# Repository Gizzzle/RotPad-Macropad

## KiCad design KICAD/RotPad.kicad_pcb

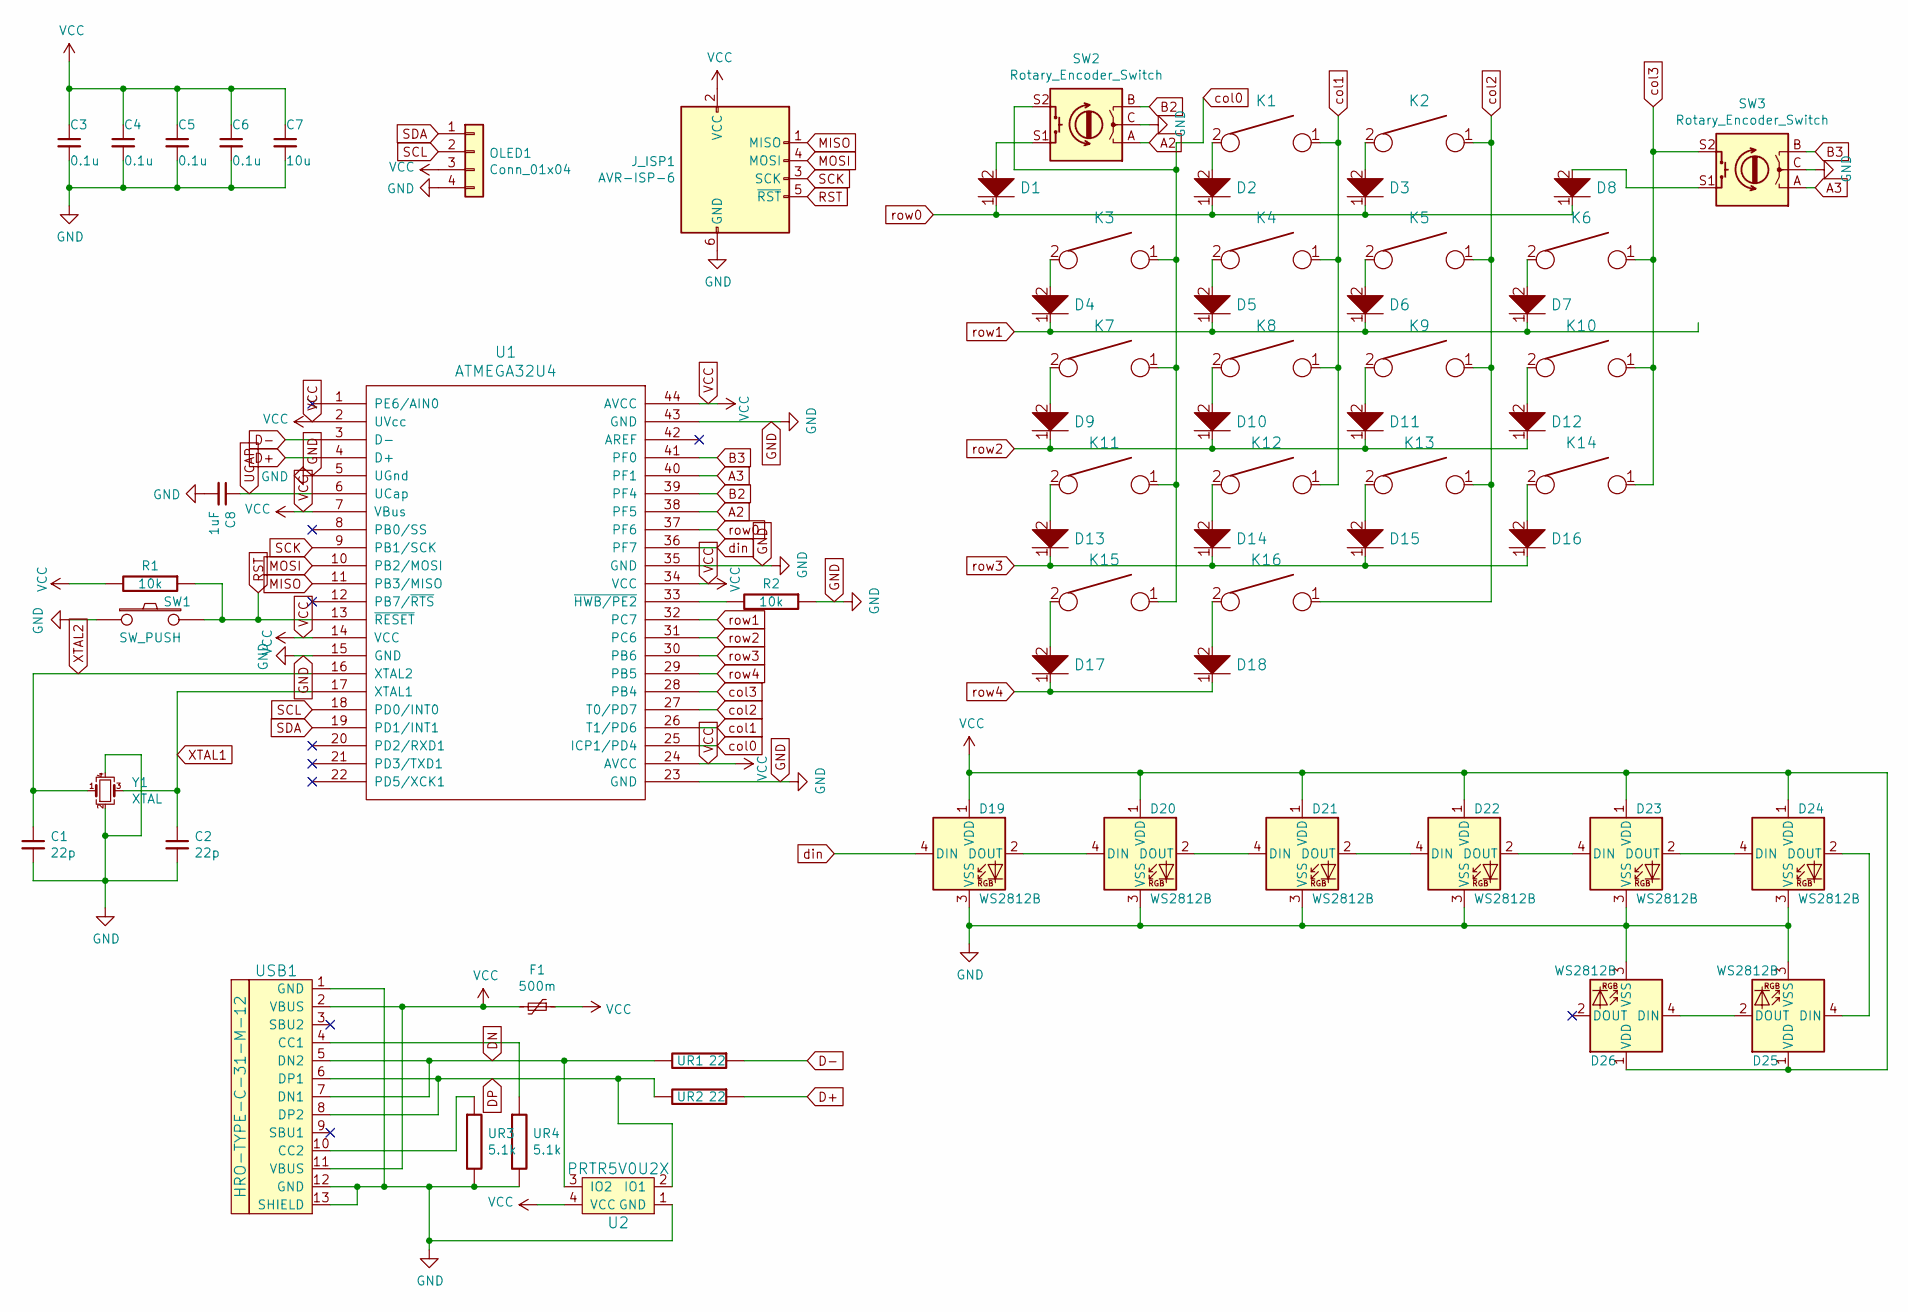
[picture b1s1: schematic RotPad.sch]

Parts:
C1, C2: 22p; C_0805_2012Metric_Pad1.15x1.40mm_HandSolder
C3, C4, C5, C6: 0.1u; C_0805_2012Metric_Pad1.15x1.40mm_HandSolder
C7: 10u; C_0805_2012Metric_Pad1.15x1.40mm_HandSolder
C8: 1uF; C_0805_2012Metric_Pad1.15x1.40mm_HandSolder
D1, D2, D3, D4, D5, D6, D7, D8, D9, D10, D11, D12, D13, D14, D15, D16, D17, D18: D; D_SOD123
D19, D20, D21, D22, D23, D24, D25, D26: WS2812B; LED_WS2812B_PLCC4_5.0x5.0mm_P3.2mm
F1: 500m; Fuse_1206_3216Metric_Pad1.42x1.75mm_HandSolder
J_ISP1: AVR-ISP-6; Reset_Pretty-Mask
K1: /; MX-1U-NoLED
K2: *; MX-1U-NoLED
K3: 7; MX-1U-NoLED
K4: 8; MX-1U-NoLED
K5: 9; MX-1U-NoLED
K6: -; MX-1U-NoLED
K7: 4; MX-1U-NoLED
K8: 5; MX-1U-NoLED
K9: 6; MX-1U-NoLED
K10: +; MX-1U-NoLED
K11: 1; MX-1U-NoLED
K12: 2; MX-1U-NoLED
K13: 3; MX-1U-NoLED
K14: ENTER; MX-2U-NoLED
K15: 0; MX-2U-NoLED
K16: ,; MX-1U-NoLED
OLED1: Conn_01x04; PinHeader_1x04_P2.54mm_Vertical
R1, R2: 10k; R_0805_2012Metric_Pad1.15x1.40mm_HandSolder
SW1: SW_PUSH; SW_SPST_TL3342
SW2, SW3: Rotary_Encoder_Switch; RotaryEncoder_Alps_EC11E-Switch_Vertical_H20mm
U1: ATMEGA32U4; TQFP-44_10x10mm_P0.8mm
U2: PRTR5V0U2X; SOT143B
UR1, UR2: 22; R_0805_2012Metric_Pad1.15x1.40mm_HandSolder
UR3, UR4: 5.1k; R_0805_2012Metric_Pad1.15x1.40mm_HandSolder
USB1: HRO-TYPE-C-31-M-12; HRO-TYPE-C-31-M-12-HandSoldering
Y1: XTAL; Crystal_SMD_3225-4Pin_3.2x2.5mm_HandSoldering

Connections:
A2: SW2.A, U1.38 (PF5)
A3: SW3.A, U1.40 (PF1)
B2: SW2.B, U1.39 (PF4)
B3: SW3.B, U1.41 (PF0)
D+: U1.4 (D+), UR2.1
D-: U1.3 (D-), UR1.1
DN: U2.3 (IO2), UR1.2, USB1.5 (DN2), USB1.7 (DN1)
DP: U2.2 (IO1), UR2.2, USB1.6 (DP1), USB1.8 (DP2)
GND: C1.2, C2.2, C3.2, C4.2, C5.2, C6.2, C7.2, C8.2, D19.3 (VSS), D20.3 (VSS), D21.3 (VSS), D22.3 (VSS), D23.3 (VSS), D24.3 (VSS), D25.3 (VSS), D26.3 (VSS), J_ISP1.6 (GND), OLED1.4, R2.1, SW1.1, SW2.C, SW3.C, U1.5 (UGnd), U1.15 (GND), U1.23 (GND), U1.35 (GND), U1.43 (GND), U2.1 (GND), UR3.2, UR4.2, USB1.1 (GND), USB1.12 (GND), USB1.13 (SHIELD), Y1.2, Y1.4
MISO: J_ISP1.1 (MISO), U1.11 (PB3/MISO)
MOSI: J_ISP1.4 (MOSI), U1.10 (PB2/MOSI)
unnamed: D1.2, SW2.S1
unnamed: D2.2, K1.2
unnamed: D3.2, K2.2
unnamed: D4.2, K3.2
unnamed: D5.2, K4.2
unnamed: D6.2, K5.2
unnamed: D7.2, K6.2
unnamed: D8.2, SW3.S1
unnamed: D9.2, K7.2
unnamed: D10.2, K8.2
unnamed: D11.2, K9.2
unnamed: D12.2, K10.2
unnamed: D13.2, K11.2
unnamed: D14.2, K12.2
unnamed: D15.2, K13.2
unnamed: D16.2, K14.2
unnamed: D17.2, K15.2
unnamed: D18.2, K16.2
unnamed: D19.2 (DOUT), D20.4 (DIN)
unnamed: D20.2 (DOUT), D21.4 (DIN)
unnamed: D21.2 (DOUT), D22.4 (DIN)
unnamed: D22.2 (DOUT), D23.4 (DIN)
unnamed: D23.2 (DOUT), D24.4 (DIN)
unnamed: D24.2 (DOUT), D25.4 (DIN)
unnamed: D25.2 (DOUT), D26.4 (DIN)
unnamed: R2.2, U1.33 (~HWB/PE2)
unnamed: UR3.1, USB1.10 (CC2)
unnamed: UR4.1, USB1.4 (CC1)
RST: J_ISP1.5 (~RST), R1.1, SW1.2, U1.13 (~RESET)
SCK: J_ISP1.3 (SCK), U1.9 (PB1/SCK)
SCL: OLED1.2, U1.18 (PD0/INT0)
SDA: OLED1.1, U1.19 (PD1/INT1)
UCAP: C8.1, U1.6 (UCap)
VCC: C3.1, C4.1, C5.1, C6.1, C7.1, D19.1 (VDD), D20.1 (VDD), D21.1 (VDD), D22.1 (VDD), D23.1 (VDD), D24.1 (VDD), D25.1 (VDD), D26.1 (VDD), F1.1, F1.2, J_ISP1.2 (VCC), OLED1.3, R1.2, U1.2 (UVcc), U1.7 (VBus), U1.14 (VCC), U1.24 (AVCC), U1.34 (VCC), U1.44 (AVCC), U2.4 (VCC), USB1.2 (VBUS), USB1.11 (VBUS)
XTAL1: C2.1, U1.17 (XTAL1), Y1.3
XTAL2: C1.1, U1.16 (XTAL2), Y1.1
col0: K3.1, K7.1, K11.1, K15.1, SW2.S2, U1.25 (ICP1/PD4)
col1: K1.1, K4.1, K8.1, K12.1, U1.26 (T1/PD6)
col2: K2.1, K5.1, K9.1, K13.1, K16.1, U1.27 (T0/PD7)
col3: K6.1, K10.1, K14.1, SW3.S2, U1.28 (PB4)
din: D19.4 (DIN), U1.36 (PF7)
row0: D1.1, D2.1, D3.1, D8.1, U1.37 (PF6)
row1: D4.1, D5.1, D6.1, D7.1, U1.32 (PC7)
row2: D9.1, D10.1, D11.1, D12.1, U1.31 (PC6)
row3: D13.1, D14.1, D15.1, D16.1, U1.30 (PB6)
row4: D17.1, D18.1, U1.29 (PB5)

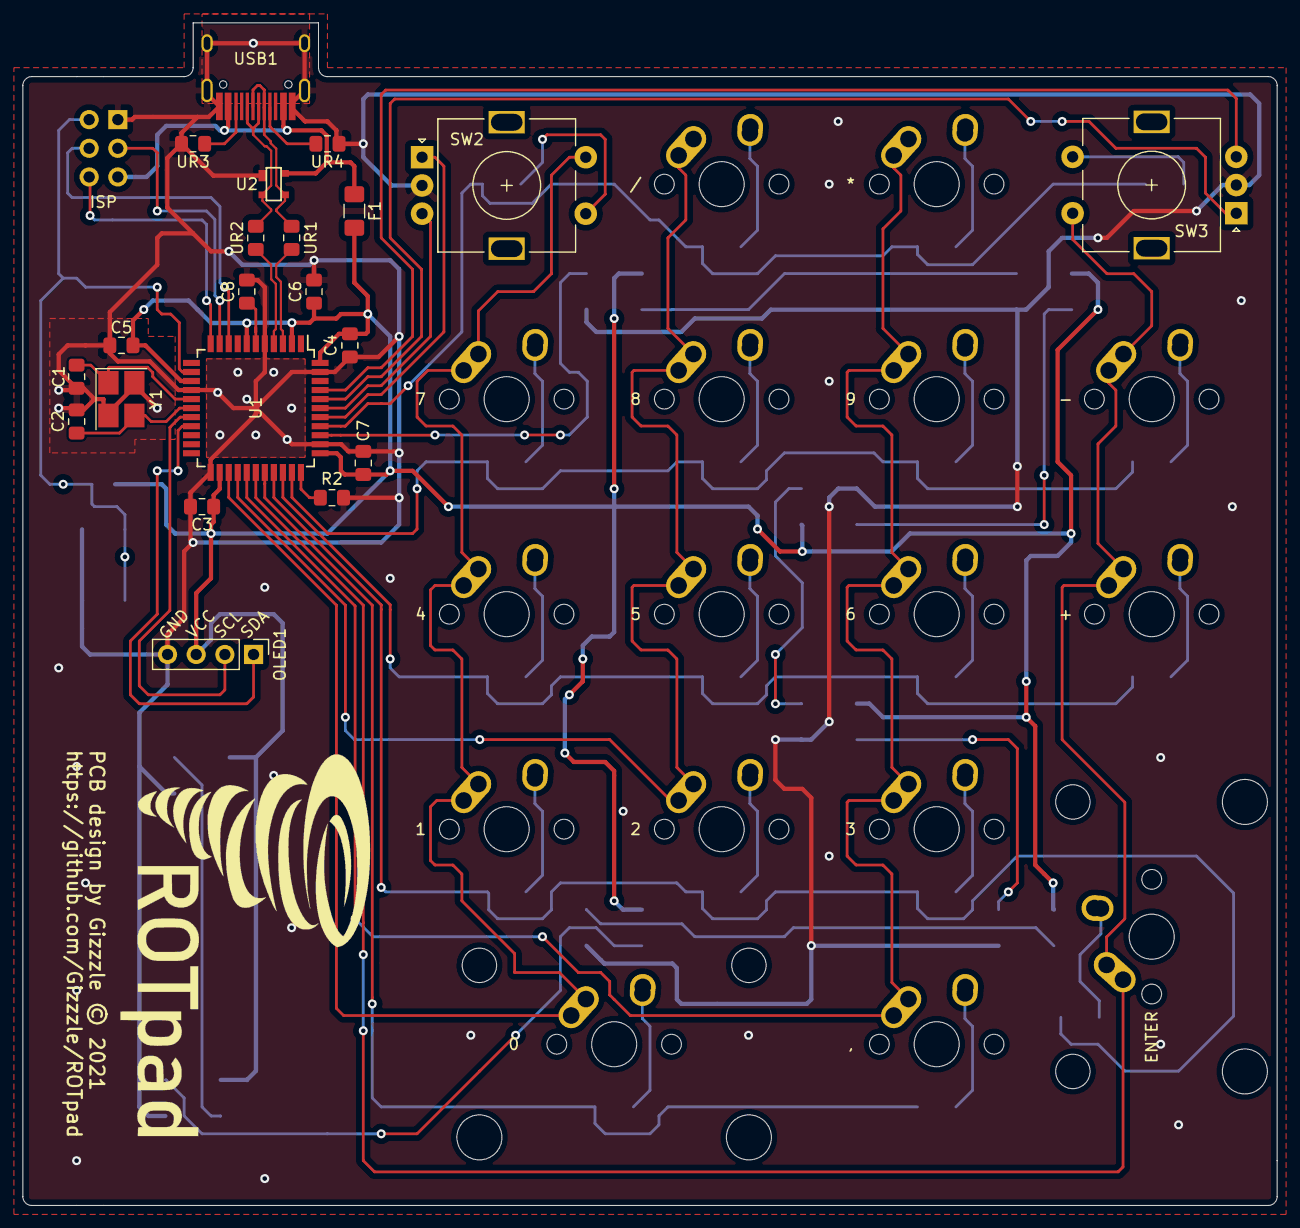
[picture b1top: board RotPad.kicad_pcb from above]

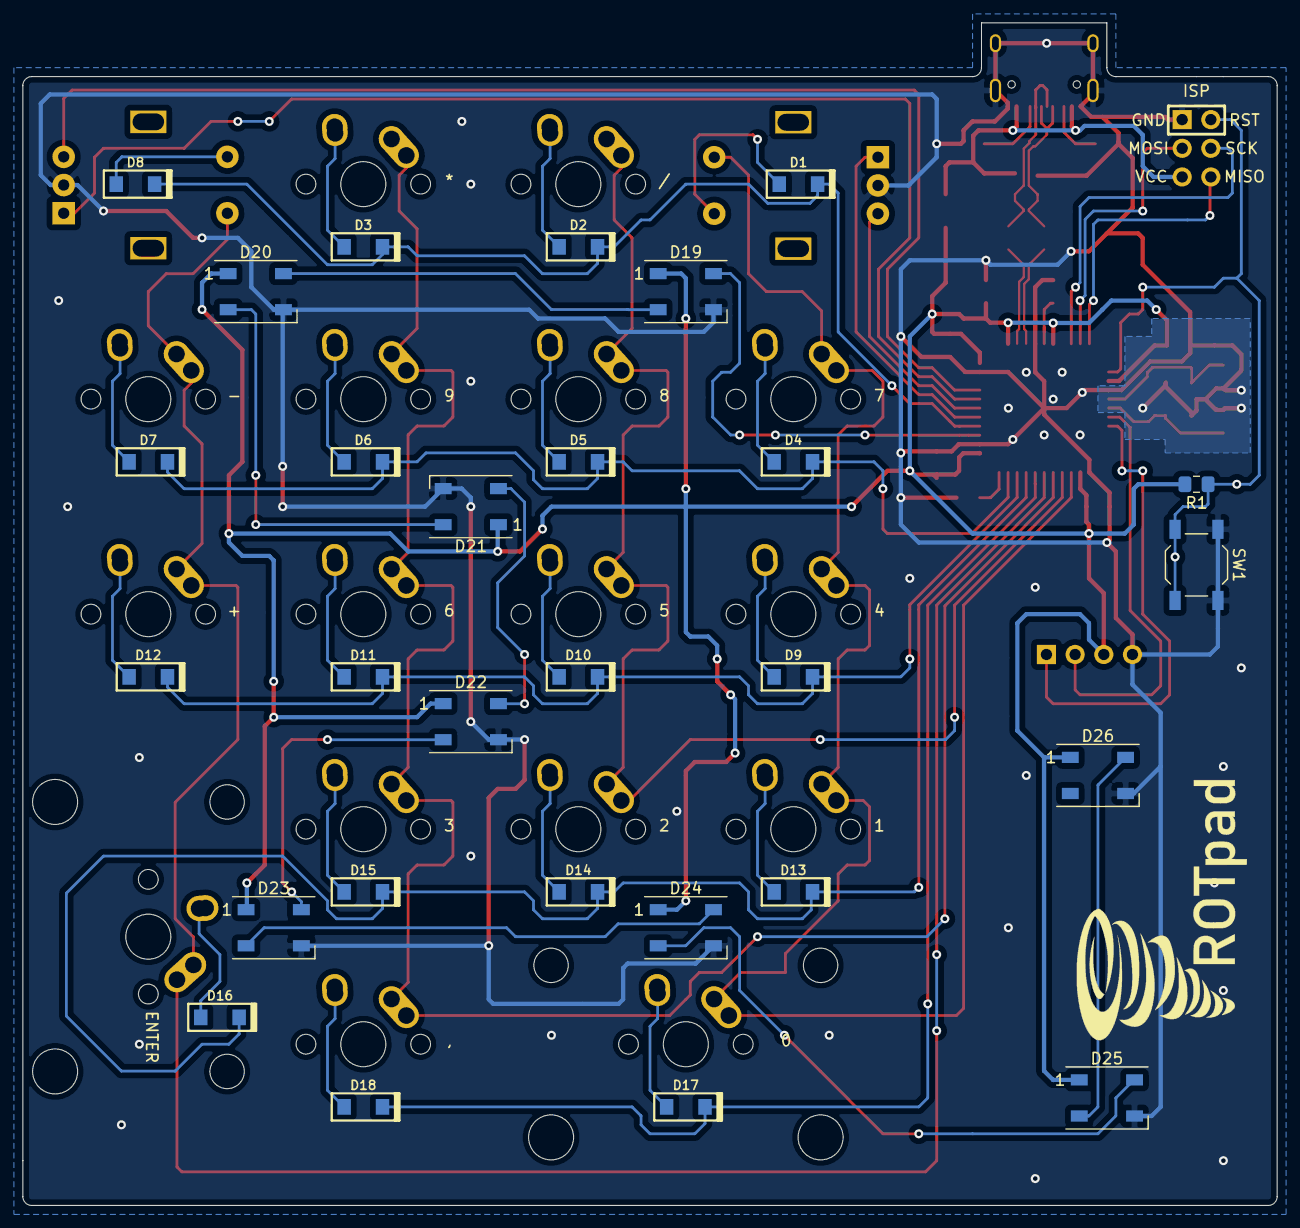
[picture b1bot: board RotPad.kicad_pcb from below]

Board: 2 copper layers, 111.1 x 104.8 mm, 66 parts (29 on the bottom side), 57 nets.

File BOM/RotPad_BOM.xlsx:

Id | Designator | Package | Part | Quantity | Supplier and ref
2 | D16,D1,D8,D18,D17,D15,D14,D13,D12,D11,D10,D9,D7,D6,D5,D4,D3,D2 | D_SOD123 | 1N4148 Switching Diode | 18 | https://lcsc.com/product-detail/Switching-Diode_Diodes-Incor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
4 | OLED1 | PinHeader_1x04_P2.54mm_Vertical | OLED Display 0.91 Inch 128 x 32 | 1 | https://de.aliexpress.com/item/32850288143.html?spm=a2g0o.pr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
5 | J_ISP1 | Reset_Pretty-Mask | Pin Header 6 Pins 2 Rows | 1
6 | K1, K2, K3, K4, K5, K6, K7, K8, K9, K10, K11, K12, K13, K14, K15, K16 | MX-1U-NoLED | Mechanical Keyswitch | 16
22 | U1 | TQFP-44_10x10mm_P0.8mm | ATMEGA32U4 | 1 | https://lcsc.com/product-detail/ATMEL-AVR_Microchip-Tech-ATM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
23 | C1,C2 | C_0805_2012Metric_Pad1.15x1.40mm_HandSolder | 22pF 0805 SMD Capacitor | 2 | https://lcsc.com/product-detail/Multilayer-Ceramic-Capacitor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
24 | D24,D19,D20,D21,D22,D23 | LED_WS2812B_PLCC4_5.0x5.0mm_P3.2mm | WS2812B LED | 6 | https://lcsc.com/product-detail/Light-Emitting-Diodes-LED_Wo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
25 | C8 | C_0805_2012Metric_Pad1.15x1.40mm_HandSolder | 1uF 0805 SMD Capacitor | 1 | https://lcsc.com/product-detail/Multilayer-Ceramic-Capacitor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
26 | Y1 | Crystal_SMD_3225-4Pin_3.2x2.5mm_HandSoldering | 16MHz Crystal | 1 | https://lcsc.com/product-detail/SMD-Crystals_YSX321SL-16MHZ-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
27 | C3,C4,C5,C6 | C_0805_2012Metric_Pad1.15x1.40mm_HandSolder | 100nF 0805 SMD Capacitor | 4 | https://lcsc.com/product-detail/Multilayer-Ceramic-Capacitor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
28 | C7 | C_0805_2012Metric_Pad1.15x1.40mm_HandSolder | 10uF 0805 SMD Capacitor | 1 | https://lcsc.com/product-detail/Multilayer-Ceramic-Capacitor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
29 | F1 | Fuse_1206_3216Metric_Pad1.42x1.75mm_HandSolder | 500mA Resettable Fuse | 1 | https://lcsc.com/product-detail/Surface-Mount-Fuses_Littelfu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
30 | R1,R2 | R_0805_2012Metric_Pad1.15x1.40mm_HandSolder | 10k 0805 SMD Resistor | 2 | https://lcsc.com/product-detail/Chip-Resistor-Surface-Mount-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
31 | SW1 | SW_SPST_TL3342 | SMD Reset Switch | 1 | https://lcsc.com/product-detail/Tactile-Switches_Korean-Hrop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
32 | SW2,SW3 | RotaryEncoder_Alps_EC11E-Switch_Vertical_H20mm | EC11E Rotary Encoder | 2 | https://lcsc.com/product-detail/Coded-Rotary-Switches_ALPSAL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
33 | U2 | SOT143B | Low Capacitance TVS Diode Array | 1 | https://lcsc.com/product-detail/TVS_TECH-PUBLIC-TPPRTR5V0U2X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
34 | UR1,UR2 | R_0805_2012Metric_Pad1.15x1.40mm_HandSolder | 22 0805 SMD Resistor | 2 | https://lcsc.com/product-detail/High-Precision-Low-TCR-SMD-R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
35 | UR3,UR4 | R_0805_2012Metric_Pad1.15x1.40mm_HandSolder | 5.1K 0805 SMD Resistor | 2 | https://lcsc.com/product-detail/Chip-Resistor-Surface-Mount_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
36 | USB1 | HRO-TYPE-C-31-M-12-HandSoldering | USB Type C Port | 1 | https://lcsc.com/product-detail/USB-Connectors_Korean-Hropar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

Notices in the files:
KICAD/RotPad.kicad_pcb:
PCB design by Gizzzle © 2021
